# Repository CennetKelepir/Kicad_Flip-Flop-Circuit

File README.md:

# Kicad_Flip Flop devresi
 Flip Flop devresi

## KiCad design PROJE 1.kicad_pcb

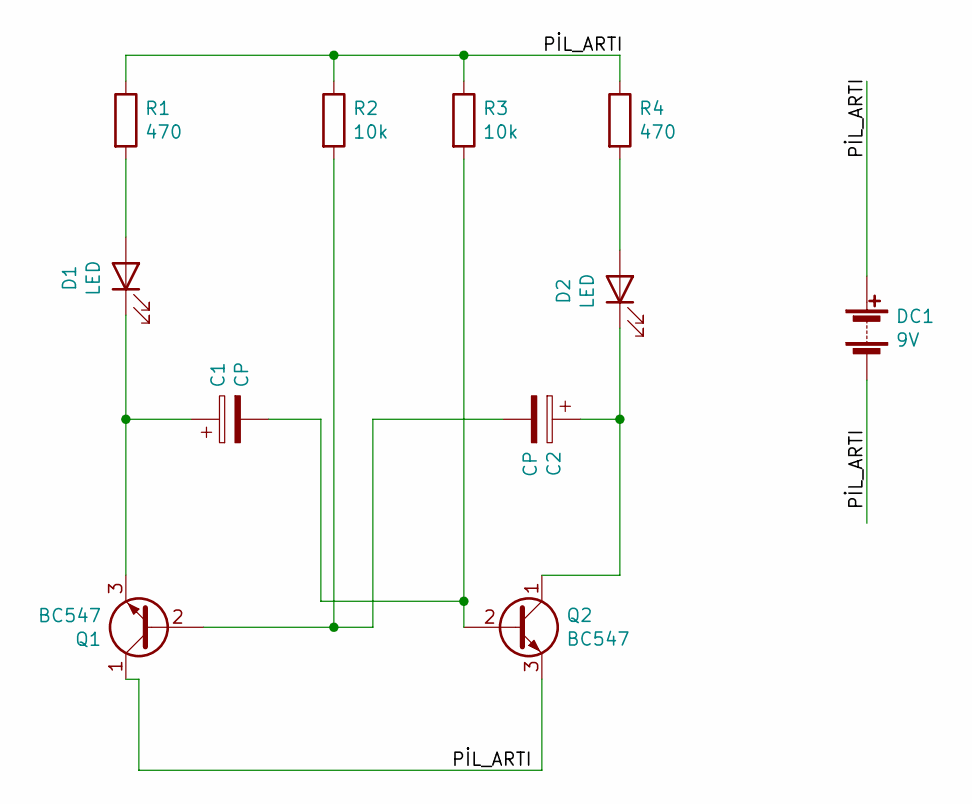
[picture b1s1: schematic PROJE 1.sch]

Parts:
C1, C2: CP; CP_Radial_Tantal_D5.0mm_P5.00mm
D1: LED; LED_D5.0mm_IRGrey
D2: LED; LED_D5.0mm_IRBlack
DC1: 9V; PinSocket_1x02_P2.54mm_Horizontal
Q1, Q2: BC547; TO-92_Inline
R1: 470; R_Axial_DIN0204_L3.6mm_D1.6mm_P5.08mm_Horizontal
R2, R3: 10k; R_Axial_DIN0204_L3.6mm_D1.6mm_P5.08mm_Horizontal
R4: 470; R_Axial_DIN0204_L3.6mm_D1.6mm_P2.54mm_Vertical

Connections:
/PİL_ARTI: DC1.1 (+), DC1.2 (-), Q1.1 (C), Q2.3 (E), R1.1, R2.1, R3.1, R4.1
unnamed: C1.1, D1.1 (K), Q1.3 (E)
unnamed: C1.2, Q2.2 (B), R3.2
unnamed: C2.1, D2.1 (K), Q2.1 (C)
unnamed: C2.2, Q1.2 (B), R2.2
unnamed: D1.2 (A), R1.2
unnamed: D2.2 (A), R4.2

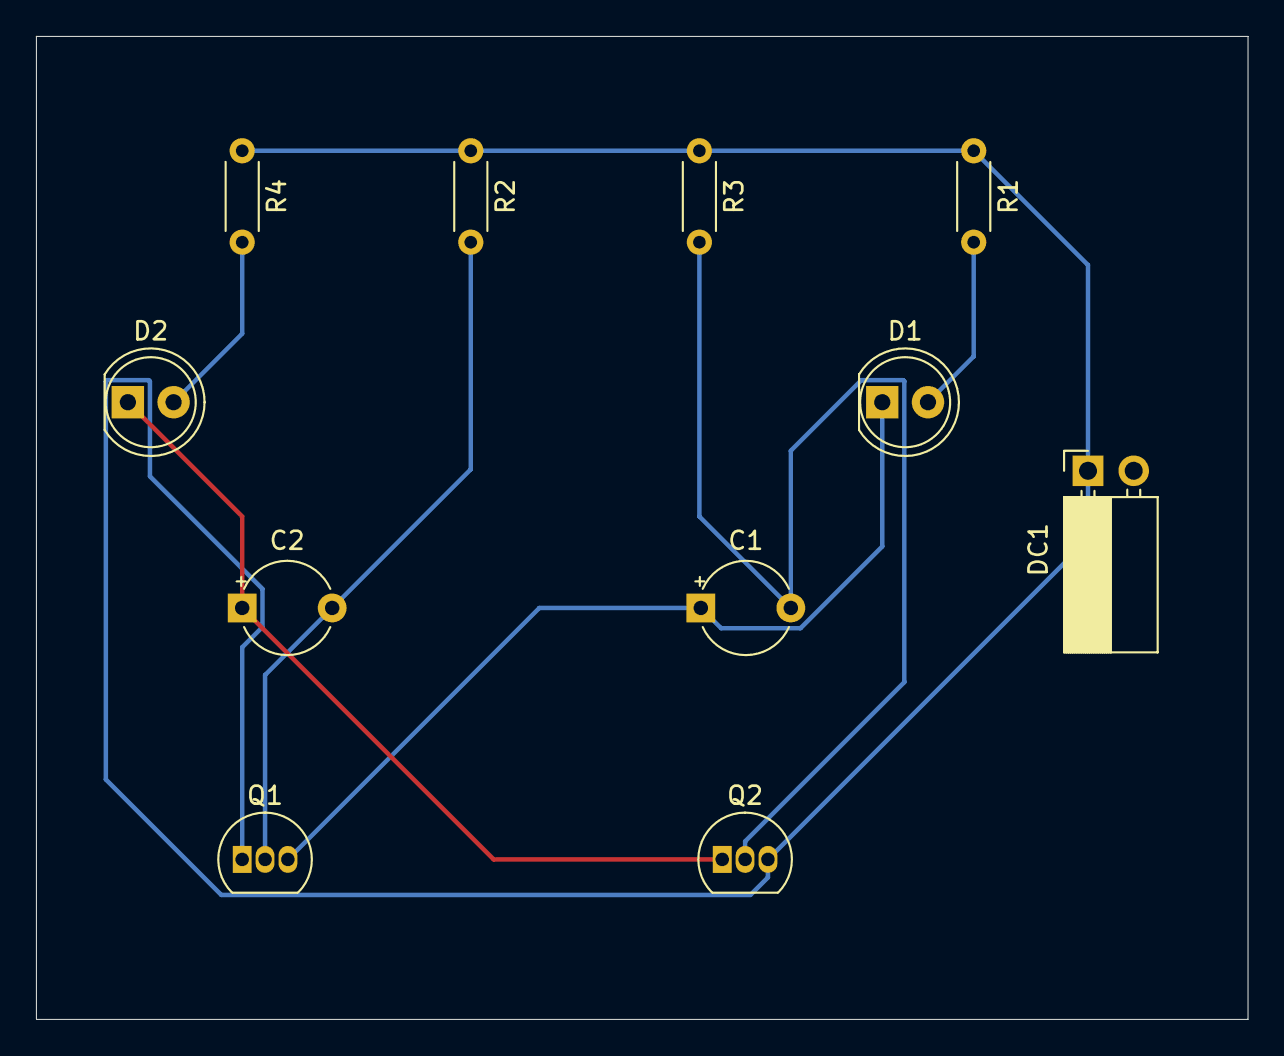
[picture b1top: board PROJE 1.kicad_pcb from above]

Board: 2 copper layers, 67.3 x 54.6 mm, 11 parts (0 on the bottom side), 7 nets.

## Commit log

2021-07-26 flipflopcircuit
2021-07-26 direnç vertical ile değiştrildi
